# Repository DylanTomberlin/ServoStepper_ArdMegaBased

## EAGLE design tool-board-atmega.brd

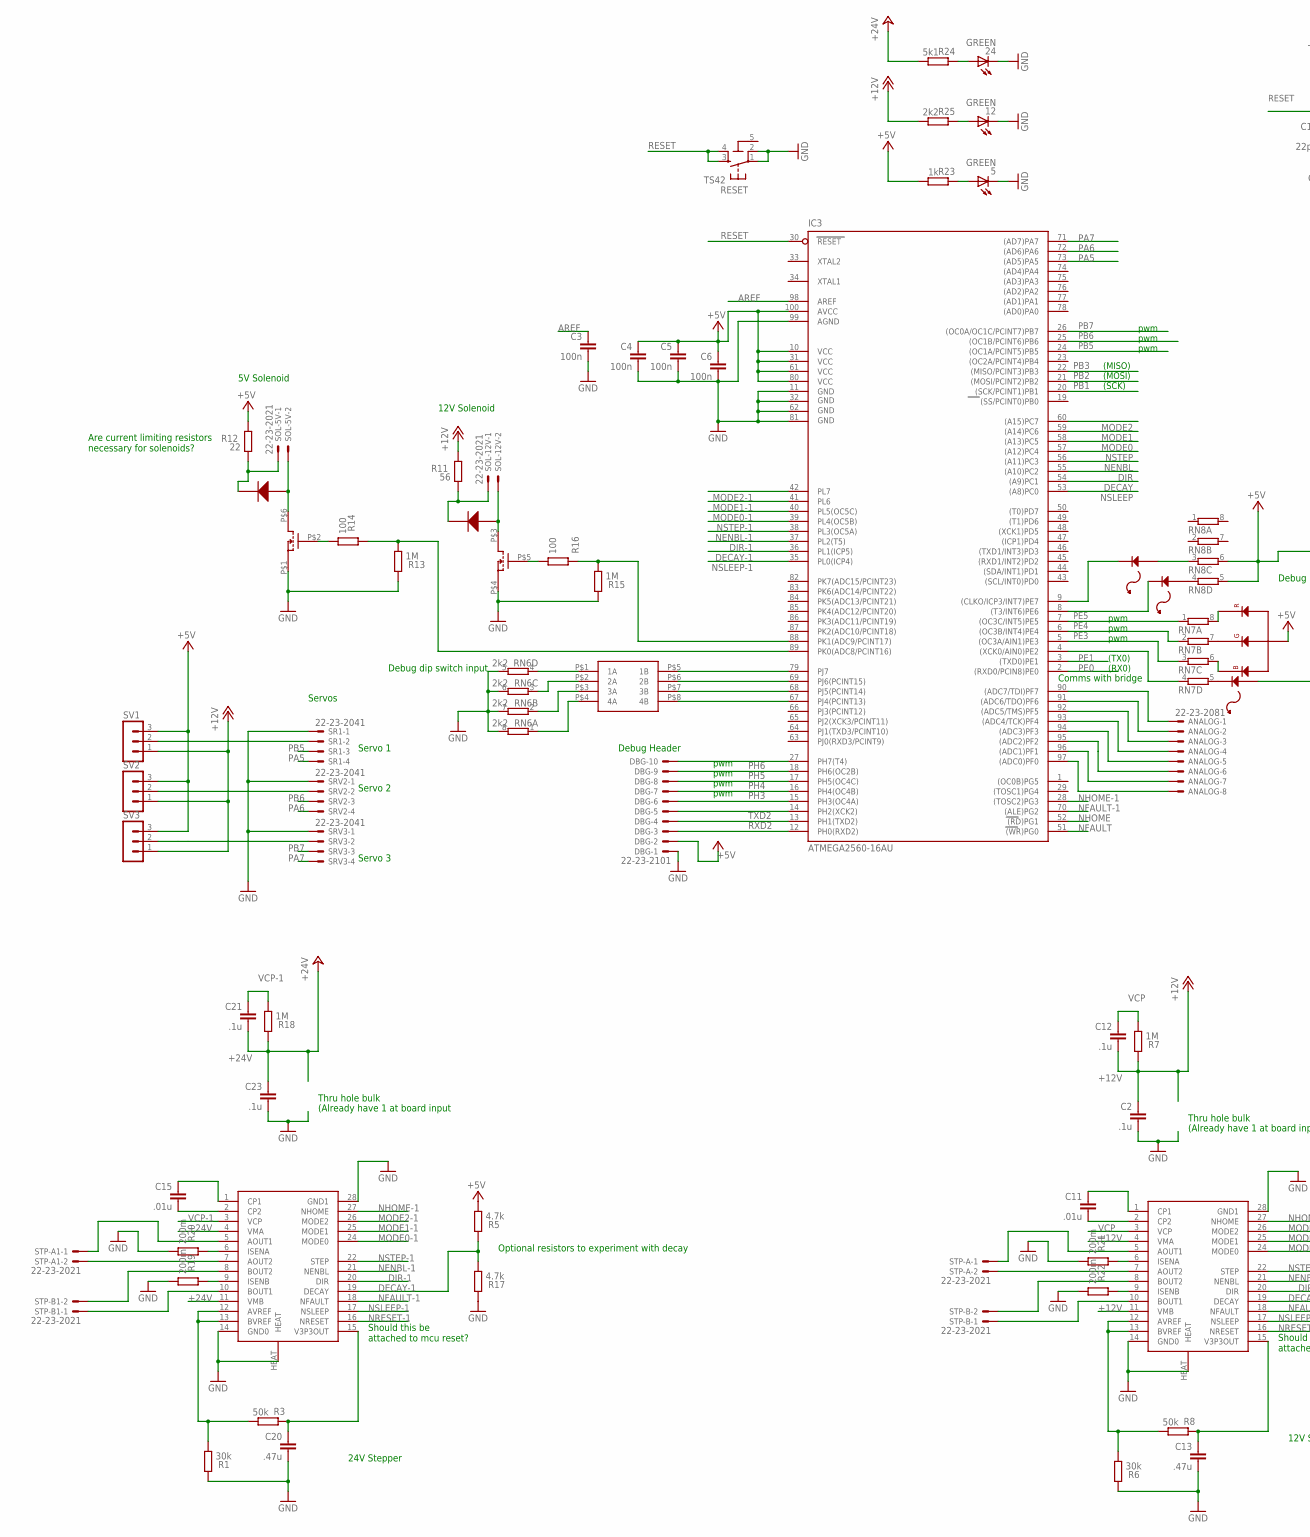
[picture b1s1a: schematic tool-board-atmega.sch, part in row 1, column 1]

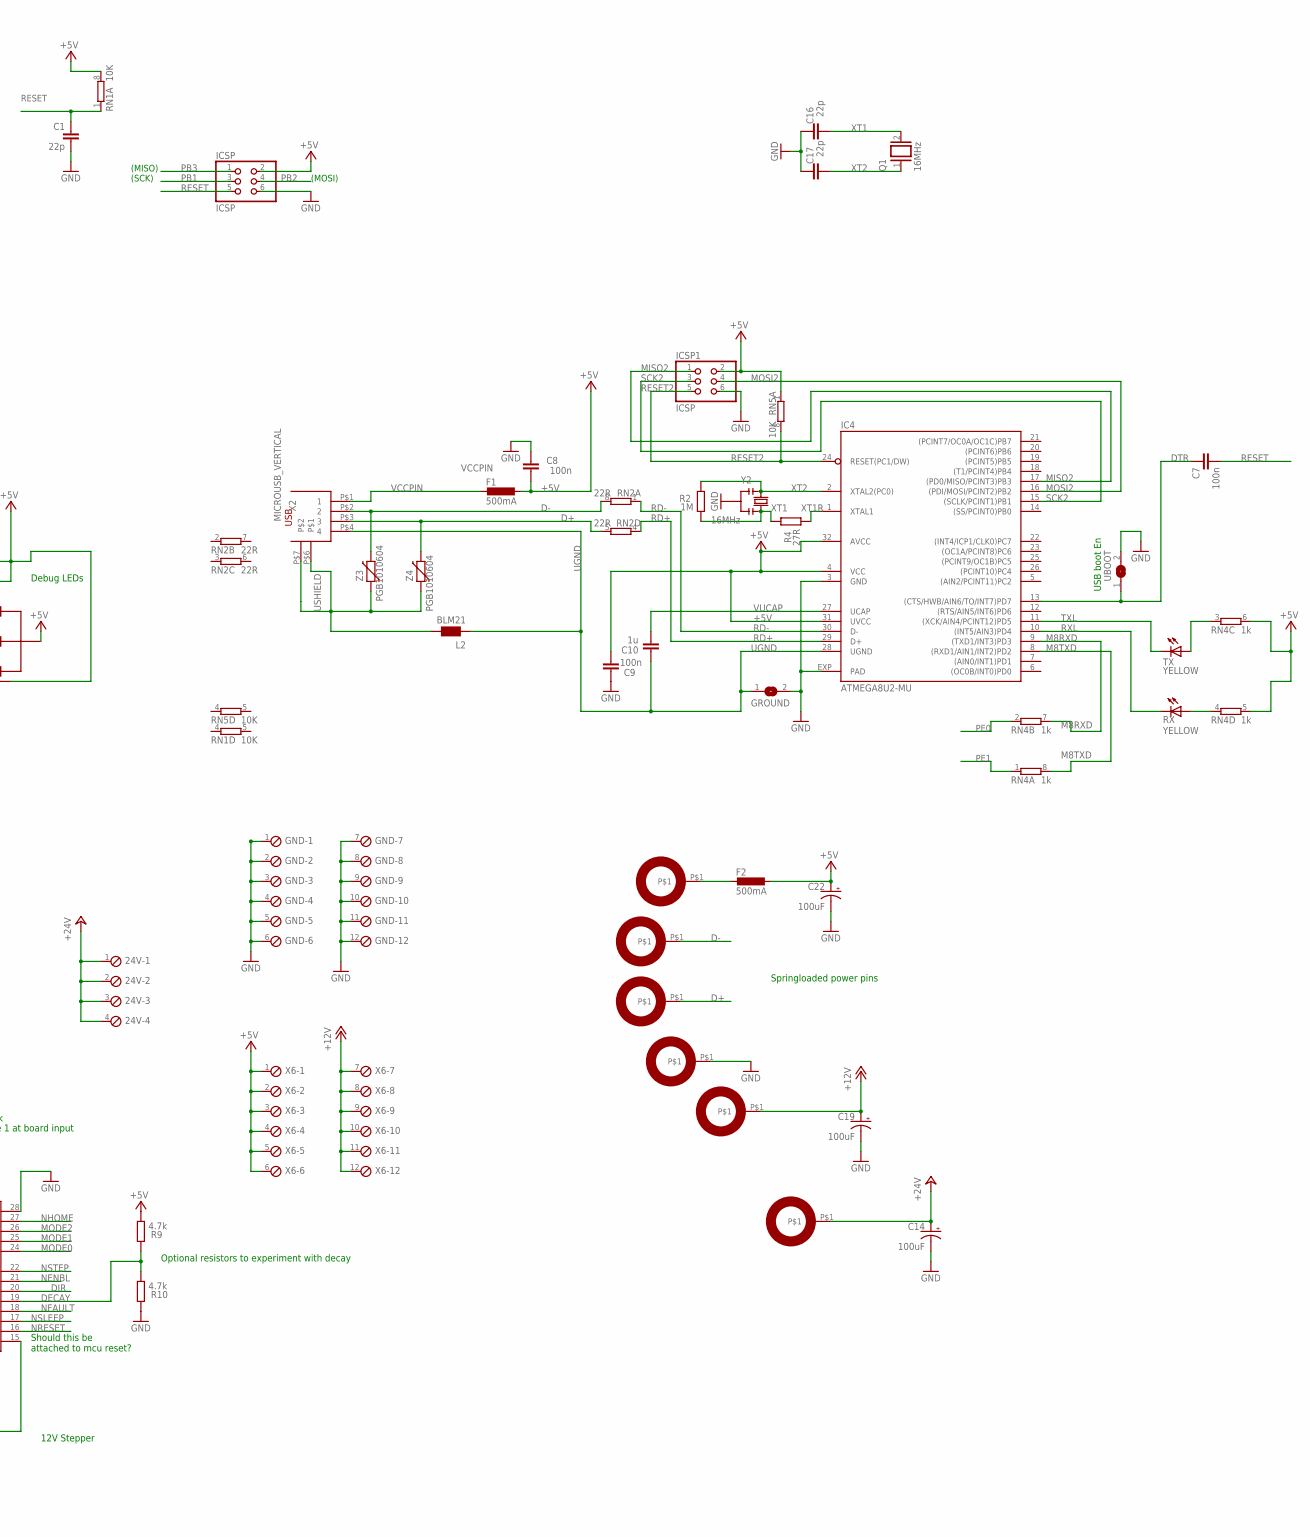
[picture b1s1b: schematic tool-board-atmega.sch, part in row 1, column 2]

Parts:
5, 12, 24: GREEN; CHIP-LED0805
24V: MPT4; 4POL254
ANALOG: 22-23-2081
C1, C16, C17: 22p; C0603-ROUND
C2, C12, C21, C23: .1u; C0603-ROUND
C3, C4, C5, C6, C7, C9: 100n; C0603-ROUND
C8: 100n; C0603
C10: 1u; C0603-ROUND
C11, C15: .01u; C0603-ROUND
C13, C20: .47u; C0603-ROUND
C14, C19, C22: 100uF; E3,5-8
DBG: 22-23-2101
F1, F2: 500mA; L1812
GND: MPT12; 12POL254
GROUND: SJ
IC3: ATMEGA2560-16AU; TQFP100
IC4: ATMEGA8U2-MU; QFN32
ICSP, ICSP1: ICSP; 2X03
L2: BLM21; 0805
Q1: 16MHz; QS
R1, R6: 30k; R0603-ROUND
R2, R7, R13, R18: 1M; R0603-ROUND
R3, R8: 50k; R0603-ROUND
R4: 27R; R0603-ROUND
R5, R9, R10, R17: 4.7k; R0603-ROUND
R11: 56; R0603-ROUND
R12: 22; R0603-ROUND
R14, R16: 100; R0603-ROUND
R15: 1M; SMARTPRJ_R0603-ROUND
R19, R20, R21, R22: 200m; R0603-ROUND
R23: 1k; R0603-ROUND
R24: 5k1; R0603-ROUND
R25: 2k2; R0603-ROUND
RESET: TS42
RN1, RN5: 10K; CAT16
RN2: 22R; CAY16
RN4: 1k; CAY16
RN6: 2k2; CAY16
RN7, RN8: 4R-NCAY16; CAY16
RX: YELLOW; CHIP-LED0805
SOL-5V, SOL-12V: 22-23-2021
SR1: 22-23-2041
SRV2, SRV3: 22-23-2041
STP1, STP2: DRV8825
STP-A, STP-A1: 22-23-2021
STP-B, STP-B1: 22-23-2021
SV1, SV2, SV3: MA03-1
TX: YELLOW; CHIP-LED0805
U$6, U$9, U$10, U$11, U$12, U$13: SPRING_CONTACT
U$8: SMD_4P_SW; SMD_4P_SWITCH
U$15: DUALNMOS-SSM6N7002KFULFCT; SC-88
U$16, U$17: 0603DIODE; SMARTPRJ_C0603-ROUND
U$18: RGBLED
U$19: 0805LED
U$20, U$21: 0603LED; SMARTPRJ_C0603-ROUND
UBOOT: SJ
X2: MICROUSB_VERTICAL; MICROUSB_VERT
X6: MPT12; 12POL254
Y2: 16MHz; RESONATOR
Z3, Z4: PGB1010604; CT/CN0603

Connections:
5-GND: RESET.5 (5-GND)
+5V: C4.1, C5.1, C6.1, C8.1, C9.1, C22.+, DBG.2, F1.1, F2.1, IC3.10 (VCC), IC3.31 (VCC1), IC3.61 (VCC2), IC3.80 (VCC3), IC3.100 (AVCC), IC4.4 (VCC), IC4.31 (UVCC), IC4.32 (AVCC), ICSP.2, ICSP1.2, R5.1, R9.1, R12.2, R23.1, RN1.8 (2), RN4.5 (2), RN4.6 (2), RN5.1, RN8.5 (2), RN8.6 (2), SV1.3, SV2.3, SV3.3, U$18.P$4, U$19.P$1 (A), X6.1, X6.2, X6.3, X6.4, X6.5, X6.6
+12V: C2.1, C12.2, C19.+, R7.2, R11.2, R25.1, STP2.4 (VMA), STP2.11 (VMB), SV1.1, SV2.1, SV3.1, U$12.P$1, X6.7, X6.8, X6.9, X6.10, X6.11, X6.12
+24V: 24V.1, 24V.2, 24V.3, 24V.4, C14.+, C21.2, C23.1, R18.2, R24.1, STP1.4 (VMA), STP1.11 (VMB), U$6.P$1
AREF: C3.1, IC3.98 (AREF)
D+: RN2.5 (2), U$13.P$1, X2.P$3 (3), Z4.2
D-: RN2.8 (2), U$10.P$1, X2.P$2 (2), Z3.2
DECAY: IC3.54 ((A9)PC1), R9.2, R10.1, STP2.19 (DECAY)
DECAY-1: IC3.36 (PL1(ICP5)), R5.2, R17.1, STP1.19 (DECAY)
DIR: IC3.55 ((A10)PC2), STP2.20 (DIR)
DIR-1: IC3.37 (PL2(T5)), STP1.20 (DIR)
DTR: C7.1, IC4.13 ((CTS/HWB/AIN6/TO/INT7)PD7), UBOOT.1
GND: 5.C, 12.C, 24.C, C1.2, C2.2, C3.2, C4.2, C5.2, C6.2, C8.2, C9.2, C13.2, C14.-, C16.2, C17.2, C19.-, C20.2, C22.-, C23.2, DBG.1, GND.1, GND.2, GND.3, GND.4, GND.5, GND.6, GND.7, GND.8, GND.9, GND.10, GND.11, GND.12, GROUND.2, IC3.11 (GND), IC3.32 (GND1), IC3.62 (GND2), IC3.81 (GND3), IC3.99 (AGND), IC4.3 (GND), IC4.EXP (PAD), ICSP.6, ICSP1.6, R1.2, R6.2, R10.2, R13.2, R15.2, R17.2, R19.1, R20.1, R21.1, R22.1, RESET.1, RESET.2, RN6.5 (2), RN6.6 (2), RN6.7 (2), RN6.8 (2), SR1.1, SRV2.1, SRV3.1, STP1.14 (GND0), STP1.28 (GND1), STP1.HEAT, STP2.14 (GND0), STP2.28 (GND1), STP2.HEAT, U$11.P$1, U$15.P$1 (S), U$15.P$4 (S), UBOOT.2, Y2.2
M8RXD: IC4.9 ((TXD1/INT3)PD3), RN4.7 (2)
M8TXD: IC4.8 ((RXD1/AIN1/INT2)PD2), RN4.8 (2)
MISO2: IC4.17 ((PD0/MISO/PCINT3)PB3), ICSP1.1
MODE0: IC3.58 ((A13)PC5), STP2.24 (MODE0)
MODE0-1: IC3.40 (PL5(OC5C)), STP1.24 (MODE0)
MODE1: IC3.59 ((A14)PC6), STP2.25 (MODE1)
MODE1-1: IC3.41 (PL6), STP1.25 (MODE1)
MODE2: IC3.60 ((A15)PC7), STP2.26 (MODE2)
MODE2-1: IC3.42 (PL7), STP1.26 (MODE2)
MOSI2: IC4.16 ((PDI/MOSI/PCINT2)PB2), ICSP1.4
unnamed: C11.1, STP2.1 (CP1)
unnamed: R14.1, U$15.P$2 (G)
unnamed: 5.A, R23.2
unnamed: C11.2, STP2.2 (CP2)
unnamed: RN6.4 (1), U$8.P$1 (1A)
unnamed: R6.1, R8.1, STP2.12 (AVREF), STP2.13 (BVREF)
unnamed: STP2.5 (AOUT1), STP-A.1
unnamed: STP2.7 (AOUT2), STP-A.2
unnamed: RN6.3 (1), U$8.P$2 (2A)
unnamed: RN6.2 (1), U$8.P$3 (3A)
unnamed: RN6.1, U$8.P$4 (4A)
unnamed: STP2.8 (BOUT2), STP-B.2
unnamed: STP2.10 (BOUT1), STP-B.1
unnamed: C13.1, R8.2, STP2.15 (V3P3OUT)
unnamed: IC3.88 (PK1(ADC9/PCINT17)), R15.1, R16.2
unnamed: IC3.89 (PK0(ADC8/PCINT16)), R13.1, R14.2
unnamed: SOL-12V.2, U$15.P$3 (D), U$16.1 (A)
unnamed: SOL-5V.2, U$15.P$6 (D), U$17.1 (A)
unnamed: R11.1, SOL-12V.1, U$16.2 (K)
unnamed: DBG.10, IC3.27 (PH7(T4))
unnamed: R12.1, SOL-5V.1, U$17.2 (K)
unnamed: DBG.5, IC3.14 (PH2(XCK2))
unnamed: RN7.6 (2), U$18.P$3
unnamed: RN7.7 (2), U$18.P$2
unnamed: RN7.8 (2), U$18.P$1
unnamed: IC3.4 ((XCK0/AIN0)PE2), RN7.4 (1)
unnamed: RN7.5 (2), U$19.P$2 (K)
unnamed: IC3.9 ((CLKO/ICP3/INT7)PE7), U$21.2 (K)
unnamed: IC3.8 ((T3/INT6)PE6), U$20.2 (K)
unnamed: RN8.4 (1), U$20.1 (A)
unnamed: RN8.3 (1), U$21.1 (A)
unnamed: IC3.67 (PJ4(PCINT13)), U$8.P$8 (4B)
unnamed: IC3.68 (PJ5(PCINT14)), U$8.P$7 (3B)
unnamed: IC3.69 (PJ6(PCINT15)), U$8.P$6 (2B)
unnamed: IC3.79 (PJ7), U$8.P$5 (1B)
unnamed: R16.1, U$15.P$5 (G)
unnamed: R19.2, STP1.9 (ISENB)
unnamed: F2.2, U$9.P$1
unnamed: C15.1, STP1.1 (CP1)
unnamed: C15.2, STP1.2 (CP2)
unnamed: C20.1, R3.2, STP1.15 (V3P3OUT)
unnamed: R1.1, R3.1, STP1.12 (AVREF), STP1.13 (BVREF)
unnamed: STP1.5 (AOUT1), STP-A1.1
unnamed: STP1.7 (AOUT2), STP-A1.2
unnamed: STP1.8 (BOUT2), STP-B1.2
unnamed: STP1.10 (BOUT1), STP-B1.1
unnamed: R20.2, STP1.6 (ISENA)
unnamed: R21.2, STP2.6 (ISENA)
unnamed: R22.2, STP2.9 (ISENB)
unnamed: ANALOG.1, IC3.90 ((ADC7/TDI)PF7)
unnamed: ANALOG.2, IC3.91 ((ADC6/TDO)PF6)
unnamed: ANALOG.3, IC3.92 ((ADC5/TMS)PF5)
unnamed: ANALOG.4, IC3.93 ((ADC4/TCK)PF4)
unnamed: RN4.4 (1), RX.A
unnamed: RN4.3 (1), TX.A
unnamed: ANALOG.5, IC3.94 ((ADC3)PF3)
unnamed: ANALOG.6, IC3.95 ((ADC2)PF2)
unnamed: ANALOG.7, IC3.96 ((ADC1)PF1)
unnamed: ANALOG.8, IC3.97 ((ADC0)PF0)
unnamed: SR1.2, SV1.2
unnamed: SRV2.2, SV2.2
unnamed: SRV3.2, SV3.2
unnamed: 24.A, R24.2
unnamed: 12.A, R25.2
NENBL: IC3.56 ((A11)PC3), STP2.21 (NENBL)
NENBL-1: IC3.38 (PL3(OC5A)), STP1.21 (NENBL)
NFAULT: IC3.51 ((WR)PG0), STP2.18 (NFAULT)
NFAULT-1: IC3.70 ((ALE)PG2), STP1.18 (NFAULT)
NHOME: IC3.52 ((RD)PG1), STP2.27 (NHOME)
NHOME-1: IC3.28 ((TOSC2)PG3), STP1.27 (NHOME)
NRESET: STP2.16 (NRESET)
NRESET-1: STP1.16 (NRESET)
NSLEEP: IC3.53 ((A8)PC0), STP2.17 (NSLEEP)
NSLEEP-1: IC3.35 (PL0(ICP4)), STP1.17 (NSLEEP)
NSTEP: IC3.57 ((A12)PC4), STP2.22 (STEP)
NSTEP-1: IC3.39 (PL4(OC5B)), STP1.22 (STEP)
PA5: IC3.73 ((AD5)PA5), SR1.4
PA6: IC3.72 ((AD6)PA6), SRV2.4
PA7: IC3.71 ((AD7)PA7), SRV3.4
PB1: IC3.20 ((SCK/PCINT1)PB1), ICSP.3
PB2: IC3.21 ((MOSI/PCINT2)PB2), ICSP.4
PB3: IC3.22 ((MISO/PCINT3)PB3), ICSP.1
PB5: IC3.24 ((OC1A/PCINT5)PB5), SR1.3
PB6: IC3.25 ((OC1B/PCINT6)PB6), SRV2.3
PB7: IC3.26 ((OC0A/OC1C/PCINT7)PB7), SRV3.3
PE0: IC3.2 ((RXD0/PCIN8)PE0), RN4.2 (1)
PE1: IC3.3 ((TXD0)PE1), RN4.1
PE3: IC3.5 ((OC3A/AIN1)PE3), RN7.3 (1)
PE4: IC3.6 ((OC3B/INT4)PE4), RN7.2 (1)
PE5: IC3.7 ((OC3C/INT5)PE5), RN7.1
PH3: DBG.6, IC3.15 (PH3(OC4A))
PH4: DBG.7, IC3.16 (PH4(OC4B))
PH5: DBG.8, IC3.17 (PH5(OC4C))
PH6: DBG.9, IC3.18 (PH6(OC2B))
RD+: IC4.29 (D+), RN2.4 (1)
RD-: IC4.30 (D-), RN2.1
RESET: C1.1, C7.2, IC3.30 (RESET), ICSP.5, RESET.3, RESET.4, RN1.1
RESET2: IC4.24 (RESET(PC1/DW)), ICSP1.5, RN5.8 (2)
RXD2: DBG.3, IC3.12 (PH0(RXD2))
RXL: IC4.10 ((INT5/AIN3)PD4), RX.C
SCK2: IC4.15 ((SCLK/PCINT1)PB1), ICSP1.3
TXD2: DBG.4, IC3.13 (PH1(TXD2))
TXL: IC4.11 ((XCK/AIN4/PCINT12)PD5), TX.C
UGND: C10.2, GROUND.1, IC4.28 (UGND), L2.1, X2.P$4 (4)
USHIELD: L2.2, X2.P$6, X2.P$7, Z3.1, Z4.1
VCCPIN: F1.2, X2.P$1 (1)
VCP: C12.1, R7.1, STP2.3 (VCP)
VCP-1: C21.1, R18.1, STP1.3 (VCP)
VUCAP: C10.1, IC4.27 (UCAP)
XT1: C16.1, Q1.2, R2.1, R4.2, Y2.3
XT1R: IC4.1 (XTAL1), R4.1
XT2: C17.1, IC4.2 (XTAL2(PC0)), Q1.1, R2.2, Y2.1

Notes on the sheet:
(SCK)
(MISO)
(MOSI)
pwm
(TX0)
(RX0)
USB boot En
Servos
Servo 1
Servo 2
Servo 3
Thru hole bulk
Should this be attached to mcu reset?
Optional resistors to experiment with decay
5V Solenoid
12V Solenoid
Are current limiting resistors necessary for solenoids?
Debug Header
Comms with bridge
Debug LEDs
Springloaded power pins
Debug dip switch input
24V Stepper
12V Stepper
(Already have 1 at board input

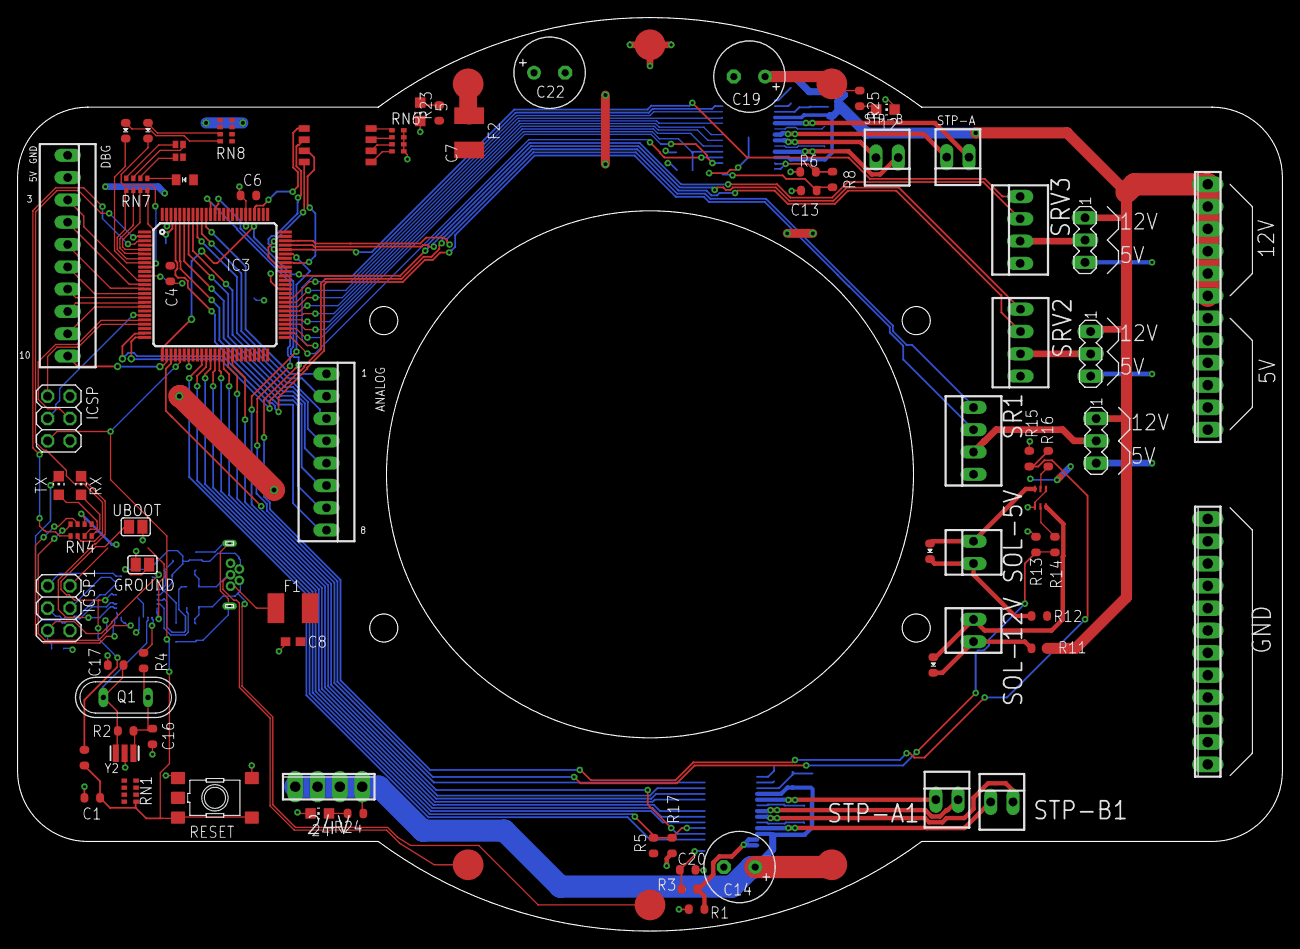
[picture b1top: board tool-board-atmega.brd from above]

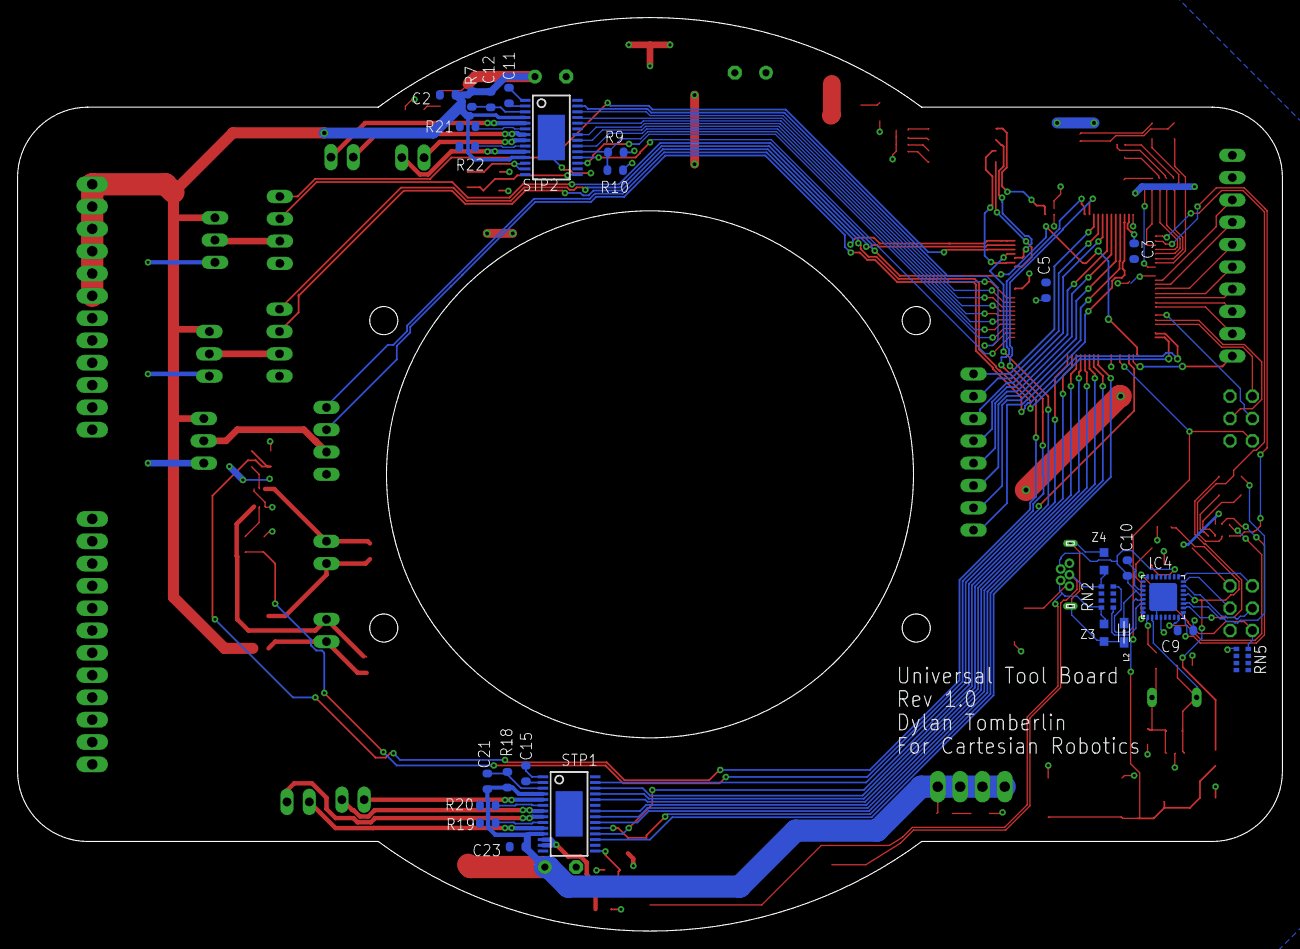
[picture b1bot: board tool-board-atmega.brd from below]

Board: 2 copper layers, 144.0 x 104.0 mm, 107 parts (26 on the bottom side), 132 nets.

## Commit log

2019-07-23 board outline planned, some larger parts placed, schematic naming tweaks
2019-07-24 schematic revision edits - thanks Jaden
2019-07-24 library updates, changed diode package, added heat pad to DRV8825
2019-07-25 riped up and started layout over, organized components into logical systems
2019-07-26 removed crystals from primary micro
2019-07-27 changed LEDs and Diodes to all be 0603 package
2019-07-31 placed all components, made Servo connectors 4 pin
2019-07-31 polys poured, local power vias placed
2019-07-31 significant routing done, need to beef up stepper related lines, add 24V stepper
2019-08-01 Beefed up 12V stepper lines, still need to work on 24V stepper lines. Need to switch connectors for higher current ones
2019-08-26 Fixed stepper motor drivers for cleaner routing, moved them closer to power pogos
2019-08-30 board Rev01 done, needs review by Jaden and to clean up labels
2019-08-30 Made revisions of Jaden's review
2019-09-10 working on labeling fixes
2019-09-10 REV 1.0
